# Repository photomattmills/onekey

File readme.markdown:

#Onekey

This is a reasonably complete set of plans for a single key programmable USB keyboard, meant to be plugged in to a usb-c connector. You could, I don't know, replace a missing escape key.

There is no code yet, but maybe there will be? The connector I made this footprint for is [this one from mouser](http://www.mouser.com/Search/ProductDetail.aspx?R=12401562E4%232Avirtualkey52350000virtualkey523-12401562E4%232A). The key is a Mattias Quiet key footprint, but any SPST switch will work. The PCB has to be thinner than standard, I recommend OSHPark's excellent [0.8mm service](http://docs.oshpark.com/services/two-layer-hhdc/). The single mounting hole is meant to take an M3 screw and nut, to act as support, so it's not stressing the connector or port as much.

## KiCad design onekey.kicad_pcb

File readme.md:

#Onekey

This is a reasonably complete set of plans for a single key programmable USB keyboard, meant to be plugged in to a usb-c connector. You could, I don't know, replace a missing escape key.

There is no code yet, but maybe there will be? The connector I made this footprint for is [this one from mouser](http://www.mouser.com/Search/ProductDetail.aspx?R=12401562E4%232Avirtualkey52350000virtualkey523-12401562E4%232A). The key is a Mattias Quiet key footprint, but any SPST switch will work. The PCB has to be thinner than standard, I recommend OSHPark's excellent [0.8mm service](http://docs.oshpark.com/services/two-layer-hhdc/). The single mounting hole is meant to take an M3 screw and nut, to act as support, so it's not stressing the connector or port as much.

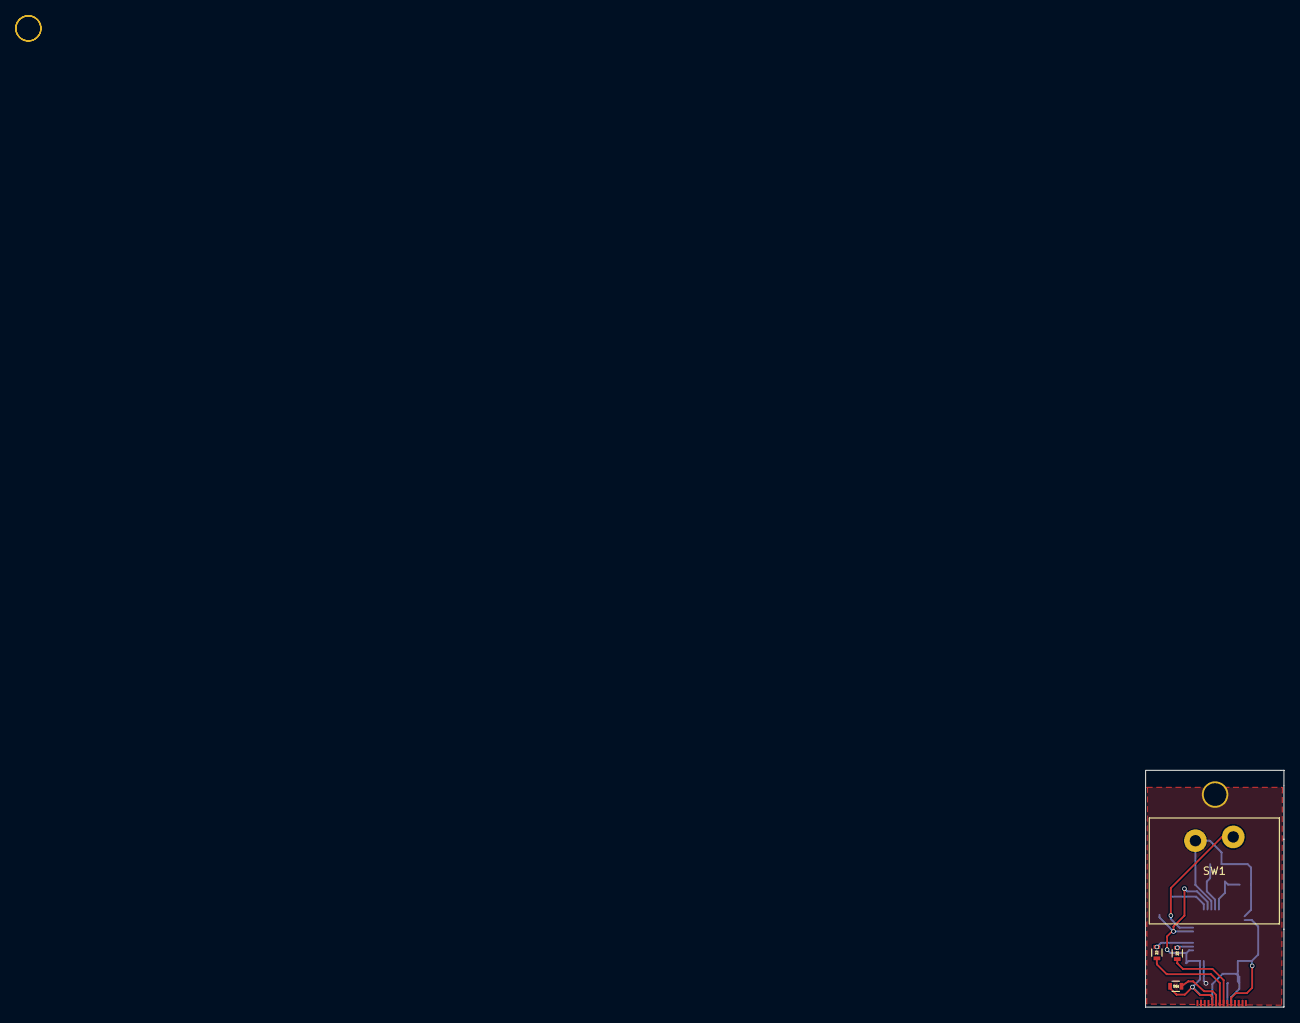
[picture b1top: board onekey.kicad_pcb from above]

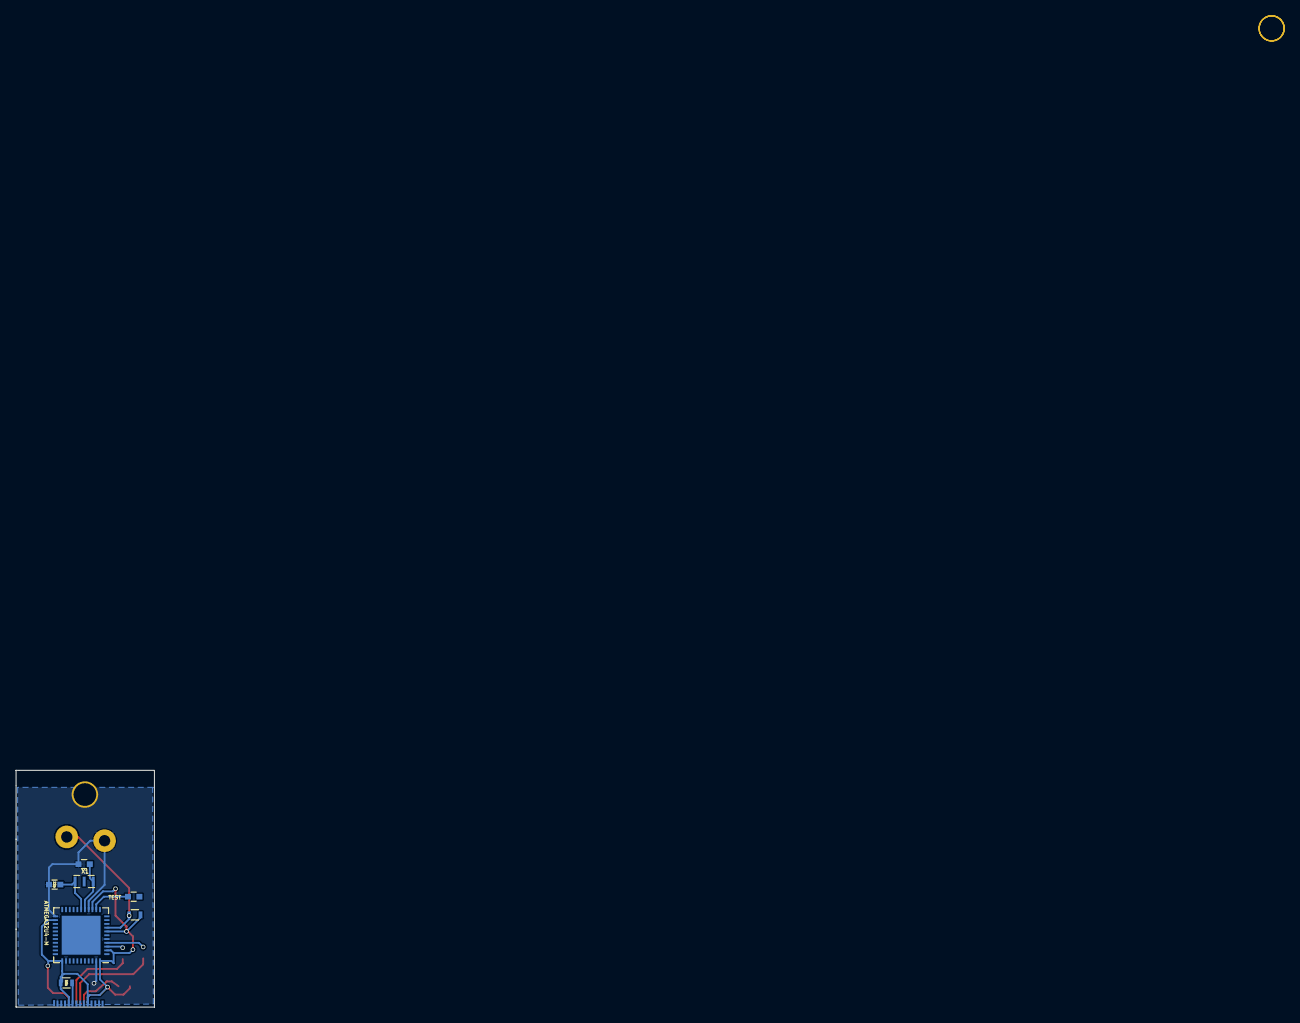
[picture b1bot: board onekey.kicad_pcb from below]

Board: 2 copper layers, 18.4 x 31.3 mm, 12 parts (7 on the bottom side), 12 nets.

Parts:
C1, C2: 22p; C_0603
R1, R2: 22; R_0603
R3: 10m; R_0603
R4, R5: 56k; R_0603
SW1: SPST; SW_Matias_Quiet
U1: ATMEGA32U4-M; QFN-44-1EP_7x7mm_Pitch0.5mm
U2: USB_TYPE_C; 12401548E4#2A-usb-c
W1: TEST; C_0603
X1: XTAL; Res_kyocera

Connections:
/D+: R1.2, U2.A6
/D-: R2.2, U2.A7
/VCC: R3.2, R4.2, R5.2, U1.2, U1.7, U1.14, U1.24, U1.34, U1.44, U2.A4, U2.A9, U2.B4, U2.B9
GND: C1.1, C2.1, SW1.1, U1.5, U1.15, U1.23, U1.35, U1.43, U2.A1, U2.A12, U2.B1, U2.B12
unnamed: C1.2, U1.17, X1.1
unnamed: C2.2, U1.16, X1.3
unnamed: R1.1, U1.4
unnamed: R2.1, U1.3
unnamed: R3.1, SW1.2, U1.8
unnamed: R4.1, U2.A5
unnamed: R5.1, U2.B5
unnamed: U1.13, W1.2

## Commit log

2016-10-26 add mounting hole for standoff
2016-10-26 add readme
2016-10-26 add readme again
